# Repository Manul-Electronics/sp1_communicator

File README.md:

# P1 Wireless Interface (P1WI)
Smart Meter serial to wireless interface (Wi-Fi).

## Configuration
1. Plug a USB-C cable in the USB-C port of the P1WI.
2. Connect the other end of the cable to your PC.
3. Start the **P1WI Utility** program and click on **Start the configuration** button. This action will start the configuration wizard.
4. When prompted to do it, select the Wi-Fi network on which the P1WI should connect. If your Wi-Fi network does not pop in the list, please verify that it operates at 2.4GHz as 5.0GHz network are not supported by the ESP32 series.
5. Once the Wi-Fi network is selected, enter you Wi-Fi password into the textbox. By default, the text is obscucated, click on **Reveal passphrase** to make it appear.
6. Click on **Next**. The P1WI should now try to connect to your network. If connection is successfuly established, the program will allow you to go to the next step. In case of failure at this step, please double check your Wi-Fi password and check that P1WI is close enough of your Wi-Fi router (the network symbol should be as full as possible).
7. The configuration is now completed and the **P1WI Utility** program should display the following message : *Configuration completed successfuly. You can now disconnect the P1WI from your computer.*
8. After you unplugged it from your computer, take the RJ11 cable and connect it to the P1 Port of your Smart Energy Meter. To do this, lift up the green/yellow cover of your Smart Energy Meter and plug it in.
9. Connect the other end of the cable to you P1WI. A red light should have been lightning up, indicating that the module is powered by the Smart Energy Meter, once connected onto your Wi-Fi, a green/yellow LED should also have been lightning up. If the connection failed, a second red LED will light up.
10. If everything went well, you can now use your P1WI.

## How to use it?

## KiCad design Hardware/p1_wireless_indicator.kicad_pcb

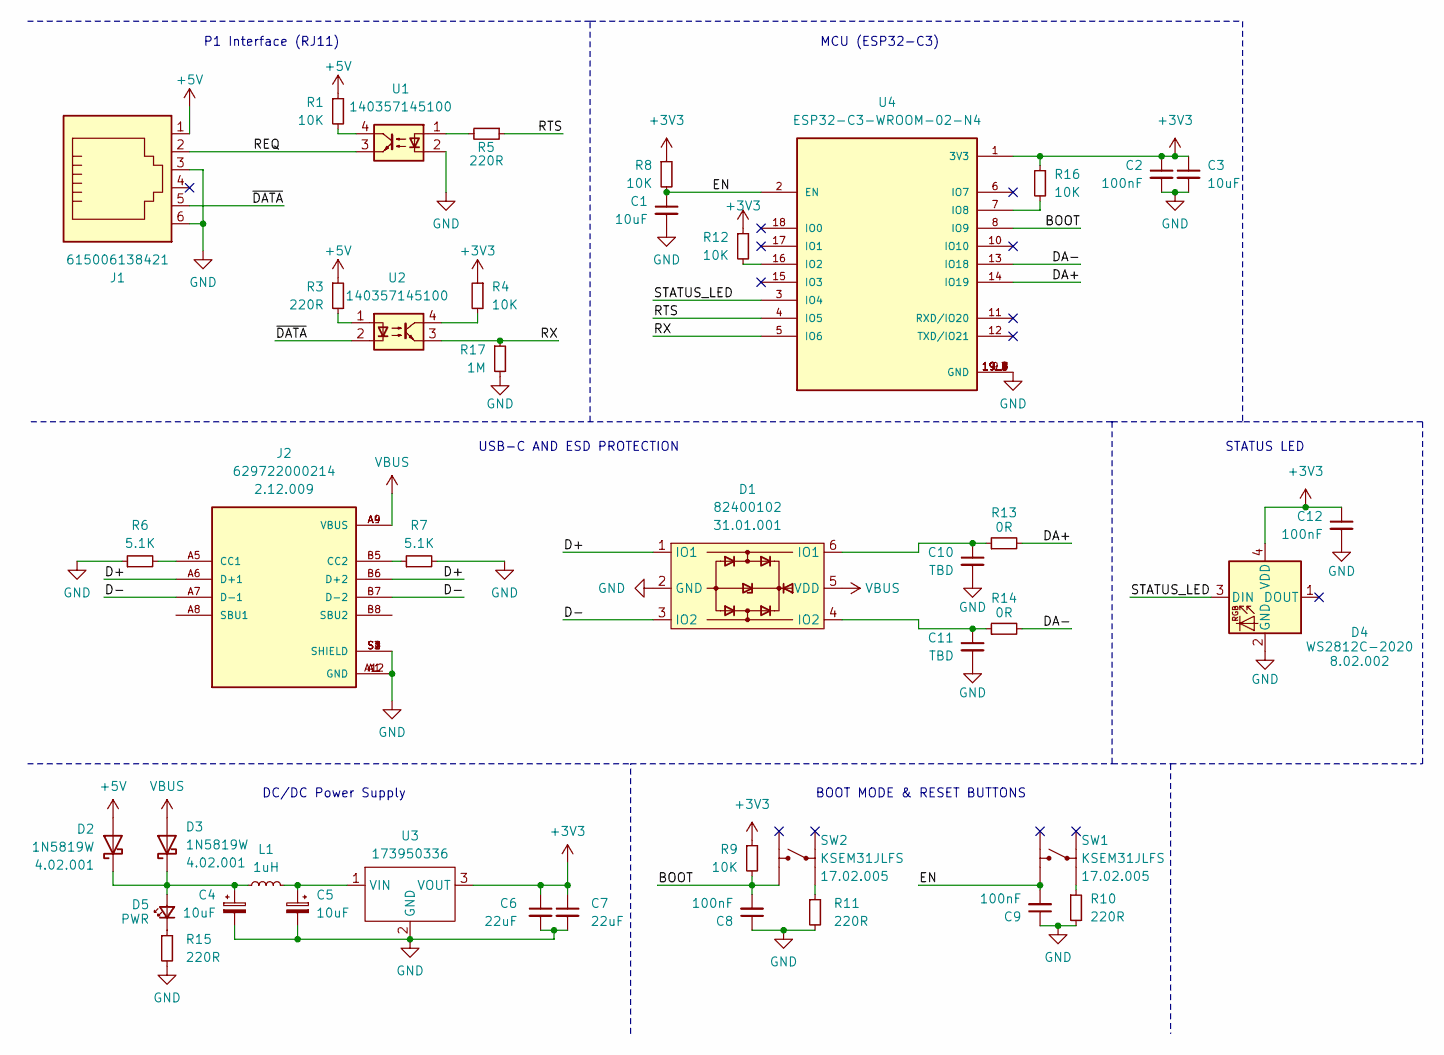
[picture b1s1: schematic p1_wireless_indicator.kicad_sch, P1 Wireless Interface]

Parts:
C1, C3: 10uF; C_0402_1005Metric; MPN 0402ZD106MAT2A
C2, C8, C9, C12: 100nF; C_0402_1005Metric; MPN 885012205037
C4, C5: 10uF; CP_Elec_6.3x5.7; MPN 875115644009
C6, C7: 22uF; C_1210_3225Metric; MPN 885012109014
C10, C11: TBD; C_0402_1005Metric
D1: 82400102; SOT-23-6; MPN 82400102
D2, D3: 1N5819W; D_SOD-123; MPN 1N5819HW-7-F
D4: WS2812C-2020; LED_WS2812C-2020; MPN WS2812C-2020
D5: PWR; LED_0402_1005Metric; MPN 150040RS73240
J1: 615006138421; MPN 615006138421
J2: 629722000214; MPN 629722000214
L1: 1uH; 7447730; MPN 7447730
R1, R4, R8, R9, R12, R16: 10K; R_0402_1005Metric; MPN CRCW040210K0FKEDHP
R3, R5, R10, R11, R15: 220R; R_0402_1005Metric; MPN CRCW0402220RFKED
R6, R7: 5.1K; R_0402_1005Metric; MPN CRCW04025K10FKED
R13, R14: 0R; R_0402_1005Metric; MPN RC0402JR-070RL
R17: 1M; R_0402_1005Metric; MPN CRCW04021M00DHEDP
SW1, SW2: KSEM31JLFS; MPN KSEM31JLFS
U1, U2: 140357145100; MPN 140357145100
U3: 173950336; SIP3_11.6x8.5mm; MPN 173950336
U4: ESP32-C3-WROOM-02-N4; MODULE_ESP32-C3-WROOM-02-H4; MPN ESP32-C3-WROOM-02-N4

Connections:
+3V3: C2.1, C3.1, C6.1, C7.1, C12.1, D4.4 (VDD), R4.1, R8.1, R9.1, R12.1, R16.1, U3.3 (VOUT), U4.1 (3V3)
+5V: D2.2 (A), J1.1, R1.1, R3.1
/BOOT: C8.2, R9.2, SW2.1, U4.8 (IO9)
/D+: D1.1 (IO1), J2.A6 (D+1), J2.B6 (D+2)
/D-: D1.3 (IO2), J2.A7 (D-1), J2.B7 (D-2)
/DA+: R13.2, U4.14 (IO19)
/DA-: R14.2, U4.13 (IO18)
/EN: C1.1, C9.2, R8.2, SW1.1, U4.2 (EN)
/REQ: J1.2, U1.3
/RTS: R5.1, U4.4 (IO5)
/RX: R17.1, U2.3, U4.5 (IO6)
/STATUS_LED: D4.3 (DIN), U4.3 (IO4)
/~DATA: J1.5, U2.2
GND: C1.2, C2.2, C3.2, C4.2, C5.2, C6.2, C7.2, C8.1, C9.1, C10.2, C11.2, C12.2, D1.2 (GND), D4.2 (GND), J1.3, J1.6, J2.A1 (GND), J2.A12 (GND), J2.S1 (SHIELD), J2.S2 (SHIELD), J2.S3 (SHIELD), J2.S4 (SHIELD), R6.1, R7.2, R10.2, R11.2, R15.2, R17.2, U1.2, U3.2 (GND), U4.9 (GND), U4.19_1 (GND), U4.19_2 (GND), U4.19_3 (GND), U4.19_4 (GND), U4.19_5 (GND), U4.19_6 (GND), U4.19_7 (GND), U4.19_8 (GND), U4.19_9 (GND)
unnamed: C10.1, D1.6 (IO1), R13.1
unnamed: C11.1, D1.4 (IO2), R14.1
unnamed: C4.1, D2.1 (K), D3.1 (K), D5.2 (A), L1.1
unnamed: D5.1 (K), R15.1
unnamed: J2.A5 (CC1), R6.2
unnamed: J2.B5 (CC2), R7.1
unnamed: R1.2, U1.4
unnamed: R3.2, U2.1
unnamed: R4.2, U2.4
unnamed: R5.2, U1.1
unnamed: R10.1, SW1.3
unnamed: R11.1, SW2.3
unnamed: C5.1, L1.2, U3.1 (VIN)
unnamed: R12.2, U4.16 (IO2)
unnamed: R16.2, U4.7 (IO8)
VBUS: D1.5 (VDD), D3.2 (A), J2.A4 (VBUS), J2.A9 (VBUS)

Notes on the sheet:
P1 Interface (RJ11)
MCU (ESP32-C3)
STATUS LED
DC/DC Power Supply
BOOT MODE & RESET BUTTONS
USB-C AND ESD PROTECTION

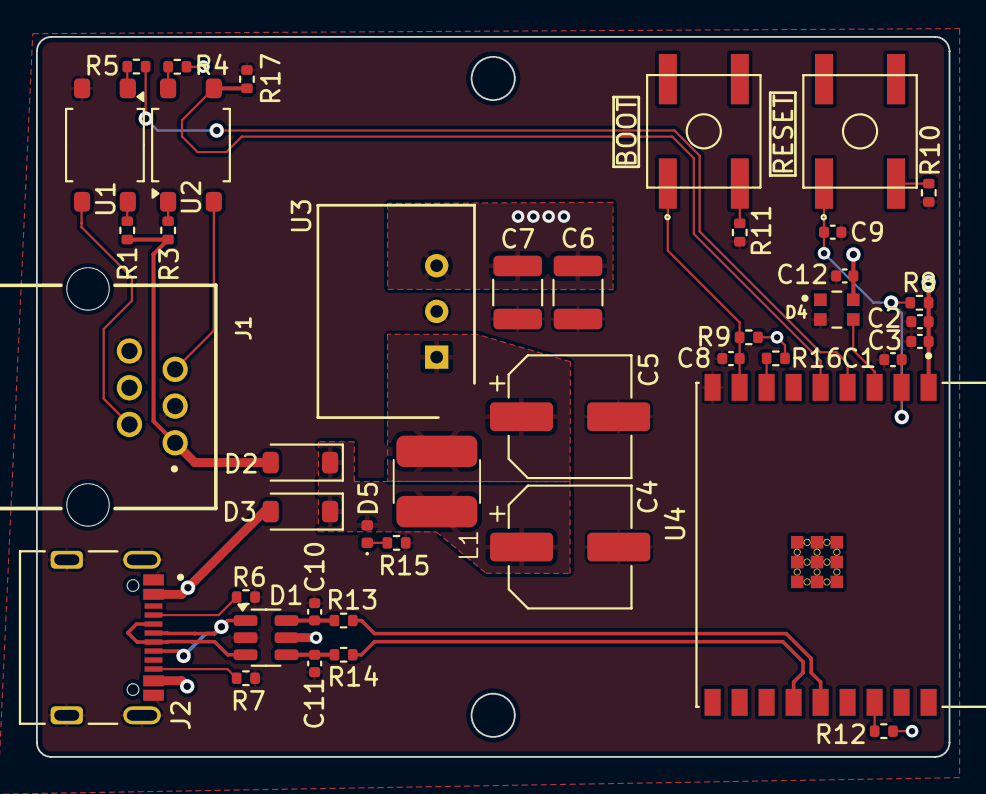
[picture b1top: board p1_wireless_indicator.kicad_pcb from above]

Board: 4 copper layers, 50.7 x 40.0 mm, 42 parts (0 on the bottom side), 30 nets.

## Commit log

2022-10-20 Renamed readme file
2022-10-20 Added KiCAD 6.0 project
2024-03-14 Rebuild p1_reader project
2024-03-16 Resumed schematic
2024-03-16 Schematic completed, started placing
2024-03-17 Completed routing
2024-03-18 Added flutter app
2024-03-18 Removed firmware file
2024-03-18 Added status led and power led and mounting holes
2024-03-20 Added missing internal references
2024-03-20 Added BOM
2024-03-21 Changed name of file
2024-03-24 Updated Layout
2024-03-24 Updated app
2024-04-01 backups
2024-04-01 Added softwares
2024-04-02 Added 10K resistor on GPIO8 to fix boot issue
2024-04-14 Output files for V1.1 replaced by V2.0
2024-04-14 Rounting of V2.0
2024-05-20 Added bom for v2.0
